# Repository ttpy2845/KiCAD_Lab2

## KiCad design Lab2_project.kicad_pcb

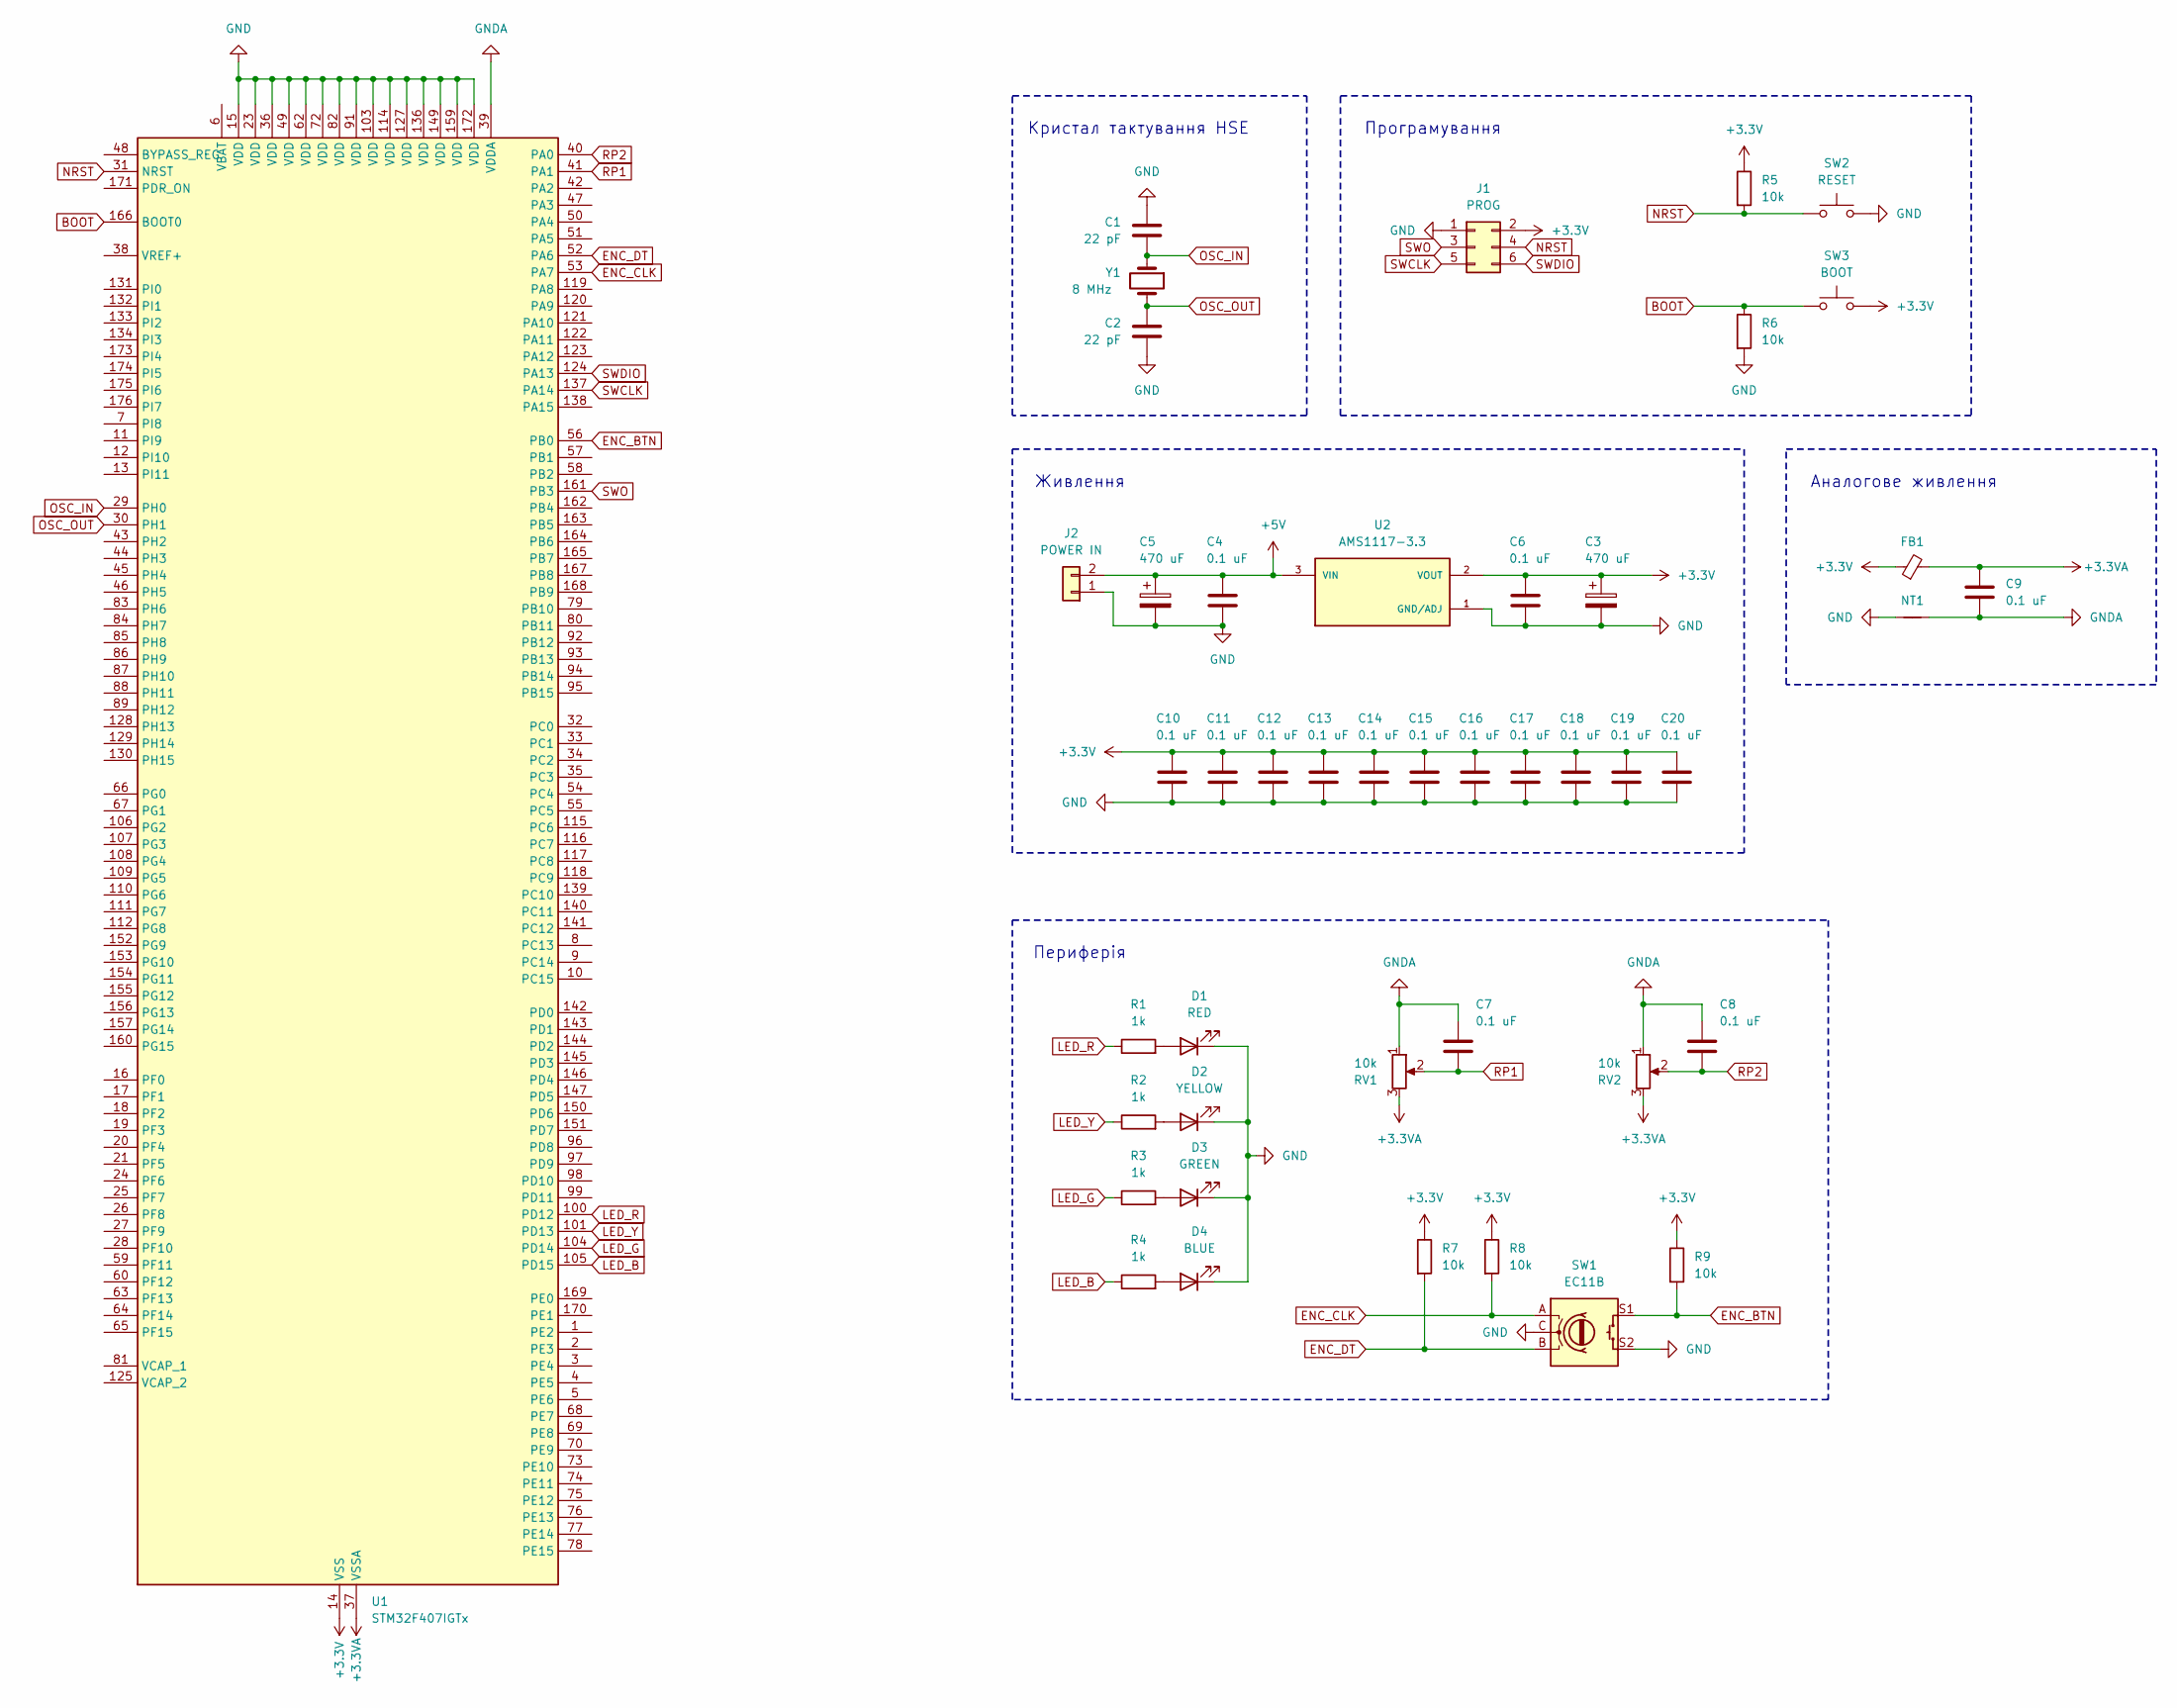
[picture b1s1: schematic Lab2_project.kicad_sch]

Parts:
C1, C2: 22 pF; C_1206_3216Metric_Pad1.33x1.80mm_HandSolder
C3, C5: 470 uF; CP_Radial_D8.0mm_P3.80mm
C4, C6, C7, C8, C9: 0.1 uF; C_1206_3216Metric_Pad1.33x1.80mm_HandSolder
C10, C11, C12, C13, C14, C15, C16, C17, C18, C19, C20: 0.1 uF; C_0805_2012Metric_Pad1.18x1.45mm_HandSolder
D1: RED; LED_D3.0mm
D2: YELLOW; LED_D3.0mm
D3: GREEN; LED_D3.0mm
D4: BLUE; LED_D3.0mm
FB1: FerriteBead_Small; LairdTech_28C0236-0JW-10
J1: PROG; PinHeader_2x03_P2.54mm_Vertical
J2: POWER IN; JST_XH_B2B-XH-A_1x02_P2.50mm_Vertical
NT1: NetTie_2; SolderJumper-2_P1.3mm_Bridged2Bar_RoundedPad1.0x1.5mm
R1, R2, R3, R4: 1k; R_1206_3216Metric_Pad1.30x1.75mm_HandSolder
R5, R6, R7, R8, R9: 10k; R_1206_3216Metric_Pad1.30x1.75mm_HandSolder
RV1, RV2: 10k; Potentiometer_Alpha_RD901F-40-00D_Single_Vertical
SW1: EC11B; RotaryEncoder_Alps_EC11E-Switch_Vertical_H20mm
SW2: RESET; SW_PUSH_6mm_H5mm
SW3: BOOT; SW_PUSH_6mm_H5mm
U1: STM32F407IGTx; LQFP-176_24x24mm_P0.5mm
U2: AMS1117-3.3; SOT-223-3_TabPin2; PARTREV N/A
Y1: 8 MHz; Crystal_HC18-U_Vertical

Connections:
+3.3V: C3.1, C6.1, C10.1, C11.1, C12.1, C13.1, C14.1, C15.1, C16.1, C17.1, C18.1, C19.1, C20.1, FB1.1, J1.2, R5.1, R7.1, R8.1, R9.1, SW3.2, U1.14 (VSS), U1.22 (VSS), U1.61 (VSS), U1.71 (VSS), U1.90 (VSS), U1.102 (VSS), U1.113 (VSS), U1.126 (VSS), U1.135 (VSS), U1.148 (VSS), U1.158 (VSS), U2.2 (VOUT)
+3.3VA: C9.1, FB1.2, RV1.3, RV2.3, U1.37 (VSSA)
+5V: C4.1, C5.1, J2.2, U2.3 (VIN)
BOOT: R6.1, SW3.1, U1.166 (BOOT0)
ENC_BTN: R9.2, SW1.S1, U1.56 (PB0)
ENC_CLK: R8.2, SW1.A, U1.53 (PA7)
ENC_DT: R7.2, SW1.B, U1.52 (PA6)
GND: C1.1, C2.2, C3.2, C4.2, C5.2, C6.2, C10.2, C11.2, C12.2, C13.2, C14.2, C15.2, C16.2, C17.2, C18.2, C19.2, C20.2, D1.1 (K), D2.1 (K), D3.1 (K), D4.1 (K), J1.1, J2.1, NT1.1, R6.2, SW1.C, SW1.S2, SW2.2, U1.15 (VDD), U1.23 (VDD), U1.36 (VDD), U1.49 (VDD), U1.62 (VDD), U1.72 (VDD), U1.82 (VDD), U1.91 (VDD), U1.103 (VDD), U1.114 (VDD), U1.127 (VDD), U1.136 (VDD), U1.149 (VDD), U1.159 (VDD), U1.172 (VDD), U2.1 (GND/ADJ)
GNDA: C7.1, C8.1, C9.2, NT1.2, RV1.1, RV2.1, U1.39 (VDDA)
LED_B: R4.1, U1.105 (PD15)
LED_G: R3.1, U1.104 (PD14)
LED_R: R1.1, U1.100 (PD12)
LED_Y: R2.1, U1.101 (PD13)
NRST: J1.4, R5.2, SW2.1, U1.31 (NRST)
unnamed: D1.2 (A), R1.2
unnamed: D2.2 (A), R2.2
unnamed: D3.2 (A), R3.2
unnamed: D4.2 (A), R4.2
OSC_IN: C1.2, U1.29 (PH0), Y1.1
OSC_OUT: C2.1, U1.30 (PH1), Y1.2
RP1: C7.2, RV1.2, U1.41 (PA1)
RP2: C8.2, RV2.2, U1.40 (PA0)
SWCLK: J1.5, U1.137 (PA14)
SWDIO: J1.6, U1.124 (PA13)
SWO: J1.3, U1.161 (PB3)

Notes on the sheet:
Периферія
Живлення
Програмування
Аналогове живлення
Кристал тактування HSE

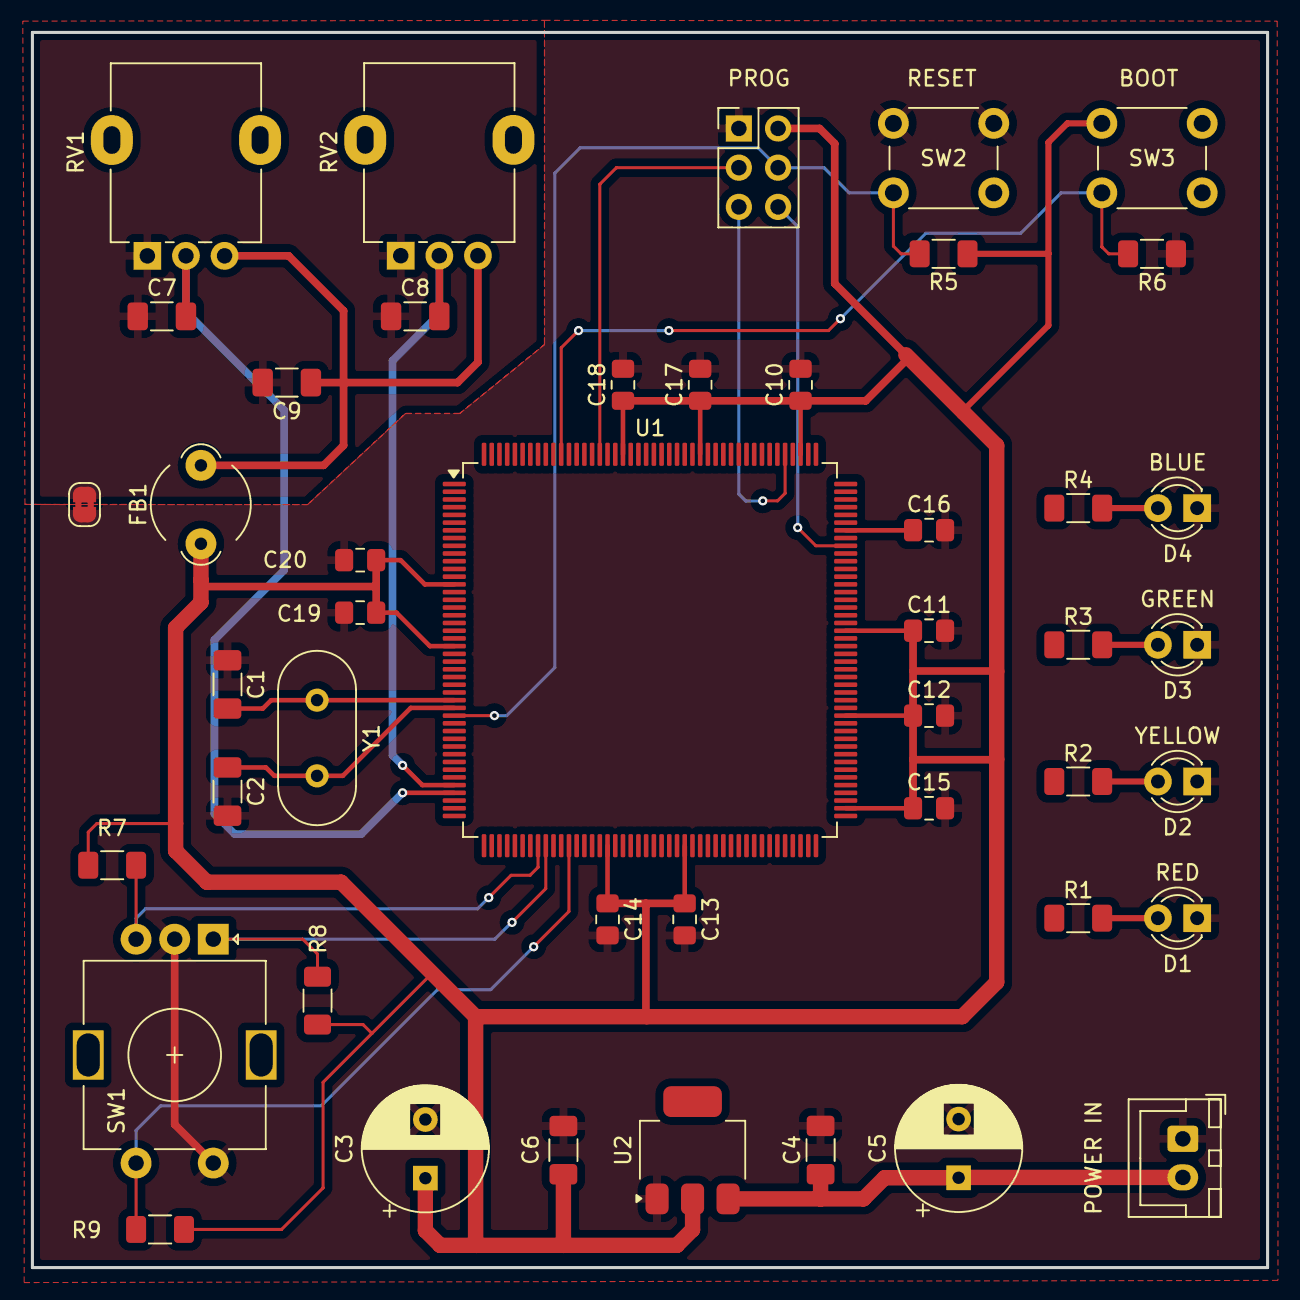
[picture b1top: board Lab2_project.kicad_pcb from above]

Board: 2 copper layers, 80.0 x 80.0 mm, 45 parts (0 on the bottom side), 25 nets.

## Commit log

2026-03-15 init commit
2026-03-16 fix: traced PCB
